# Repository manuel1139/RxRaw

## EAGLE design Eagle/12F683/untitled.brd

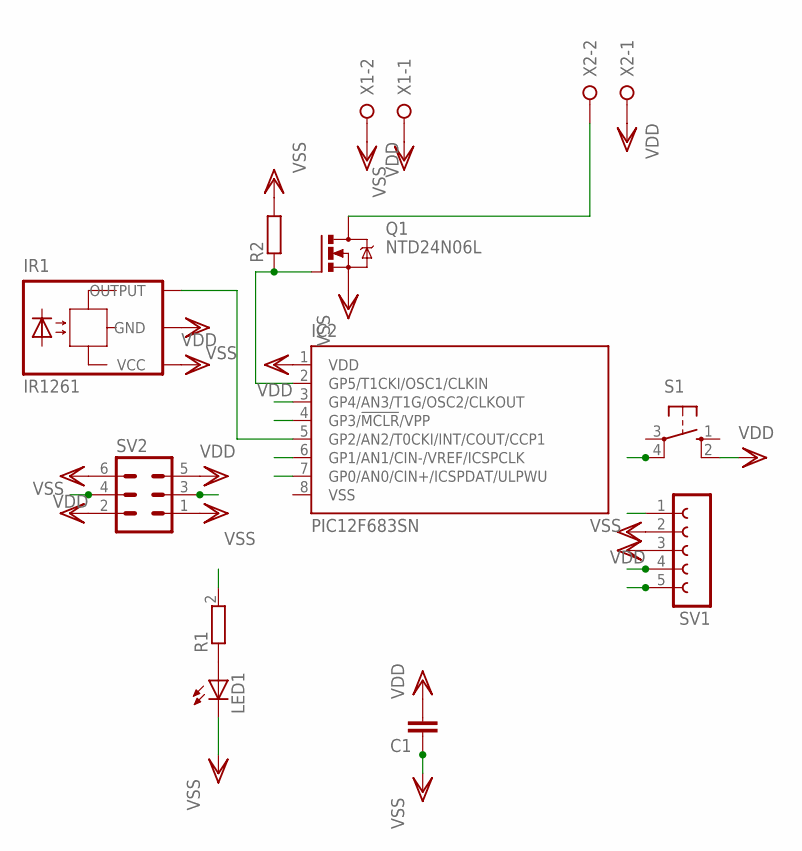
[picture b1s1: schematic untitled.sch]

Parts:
C1: C-EUC0805; C0805
IC2: PIC12F683SN; SO-08
IR1: IR1261
LED1: LEDCHIP-LED0603; CHIP-LED0603
Q1: NTD24N06L; D-PAK_TO252AA
R1: R0805_SMALL
R2: R-EU_R0805; R0805
S1: 10-XX; B3F-10XX
SV1: FE05-1
SV2: MA03-2
X1, X2: W237-02P; W237-132

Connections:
MCLR: IC2.4 (GP3/!MCLR!/VPP), SV1.1, SV2.4
unnamed: IC2.5 (GP2/AN2/T0CKI/INT/COUT/CCP1), IR1.VO (OUTPUT)
unnamed: LED1.A, R1.1 (A)
unnamed: IC2.2 (GP5/T1CKI/OSC1/CLKIN), Q1.1 (G), R2.1
unnamed: Q1.4 (D), X2.2
PGC: IC2.6 (GP1/AN1/CIN-/VREF/ICSPCLK), R1.2 (B), SV1.5
PGD: IC2.7 (GP0/AN0/CIN+/ICSPDAT/ULPWU), SV1.4, SV2.3
S1: IC2.3 (GP4/AN3/T1G/OSC2/CLKOUT), S1.4 (P1)
VDD: C1.2, IC2.1 (VDD), IR1.VCC, S1.2 (S1), SV1.2, SV2.5, SV2.6, X1.2, X2.1
VSS: C1.1, IC2.8 (VSS), IR1.GND, LED1.C, Q1.3 (S), R2.2, SV1.3, SV2.1, SV2.2, X1.1

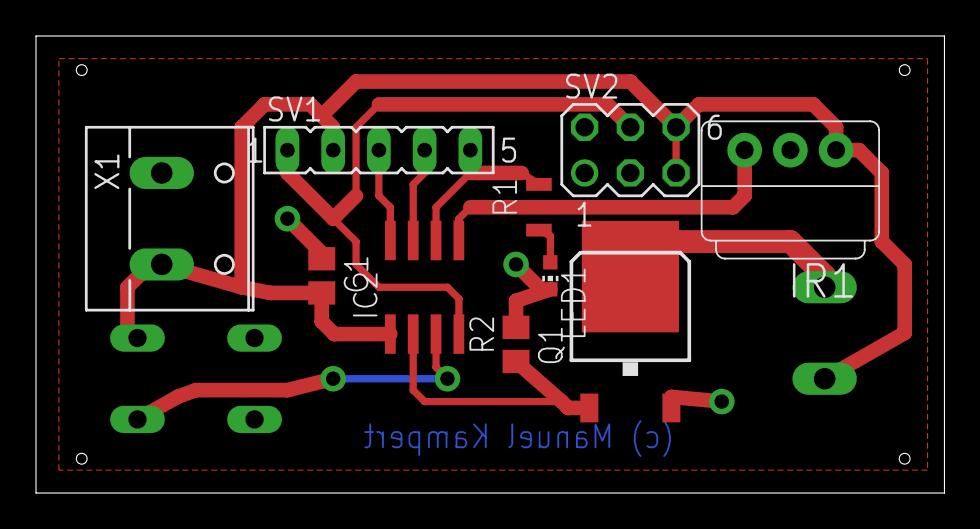
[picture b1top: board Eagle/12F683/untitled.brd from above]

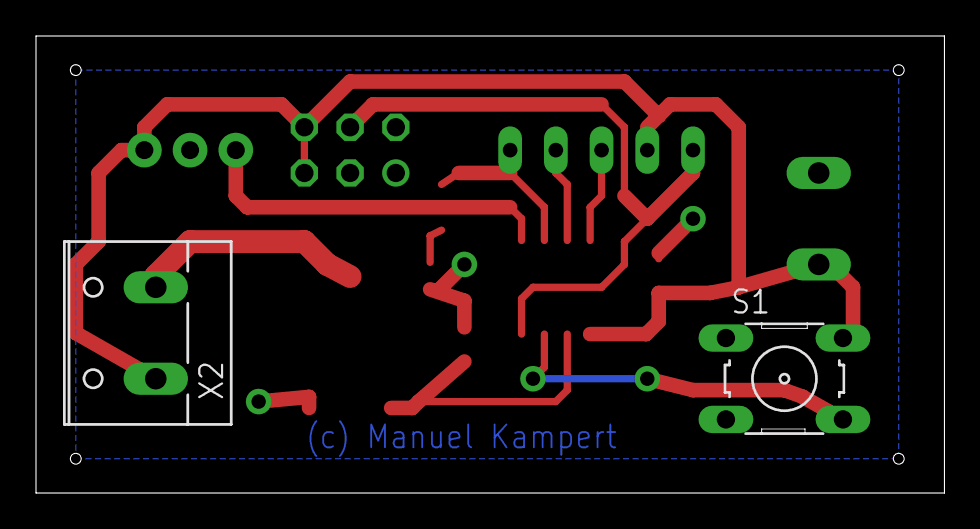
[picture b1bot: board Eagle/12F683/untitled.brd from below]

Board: 2 copper layers, 50.5 x 25.4 mm, 12 parts (2 on the bottom side), 10 nets.

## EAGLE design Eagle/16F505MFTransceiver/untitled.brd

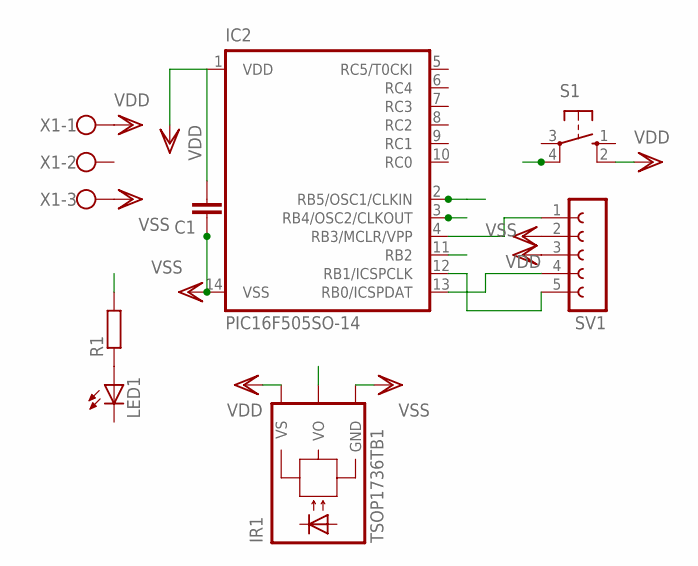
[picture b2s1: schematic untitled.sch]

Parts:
C1: C-EUC0805; C0805
IC2: PIC16F505SO-14; SO-14
IR1: TSOP1736TB1; TSOP17_TB1
LED1: LEDCHIP-LED0603; CHIP-LED0603
R1: R-EU_R0805; R0805
S1: 10-XX; B3F-10XX
SV1: FE05-1
X1: W237-103

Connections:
unnamed: IC2.4 (RB3/MCLR/VPP), SV1.1
unnamed: LED1.A, R1.1
unnamed: IC2.13 (RB0/ICSPDAT), SV1.4
unnamed: IC2.12 (RB1/ICSPCLK), SV1.5
RB2: IC2.11 (RB2), S1.4 (P1)
RB4: IC2.3 (RB4/OSC2/CLKOUT), R1.2
RB5: IC2.2 (RB5/OSC1/CLKIN), IR1.VO
VDD: C1.2, IC2.1 (VDD), IR1.VS, S1.2 (S1), SV1.2, X1.1
VSS: C1.1, IC2.14 (VSS), IR1.GND, SV1.3, X1.3

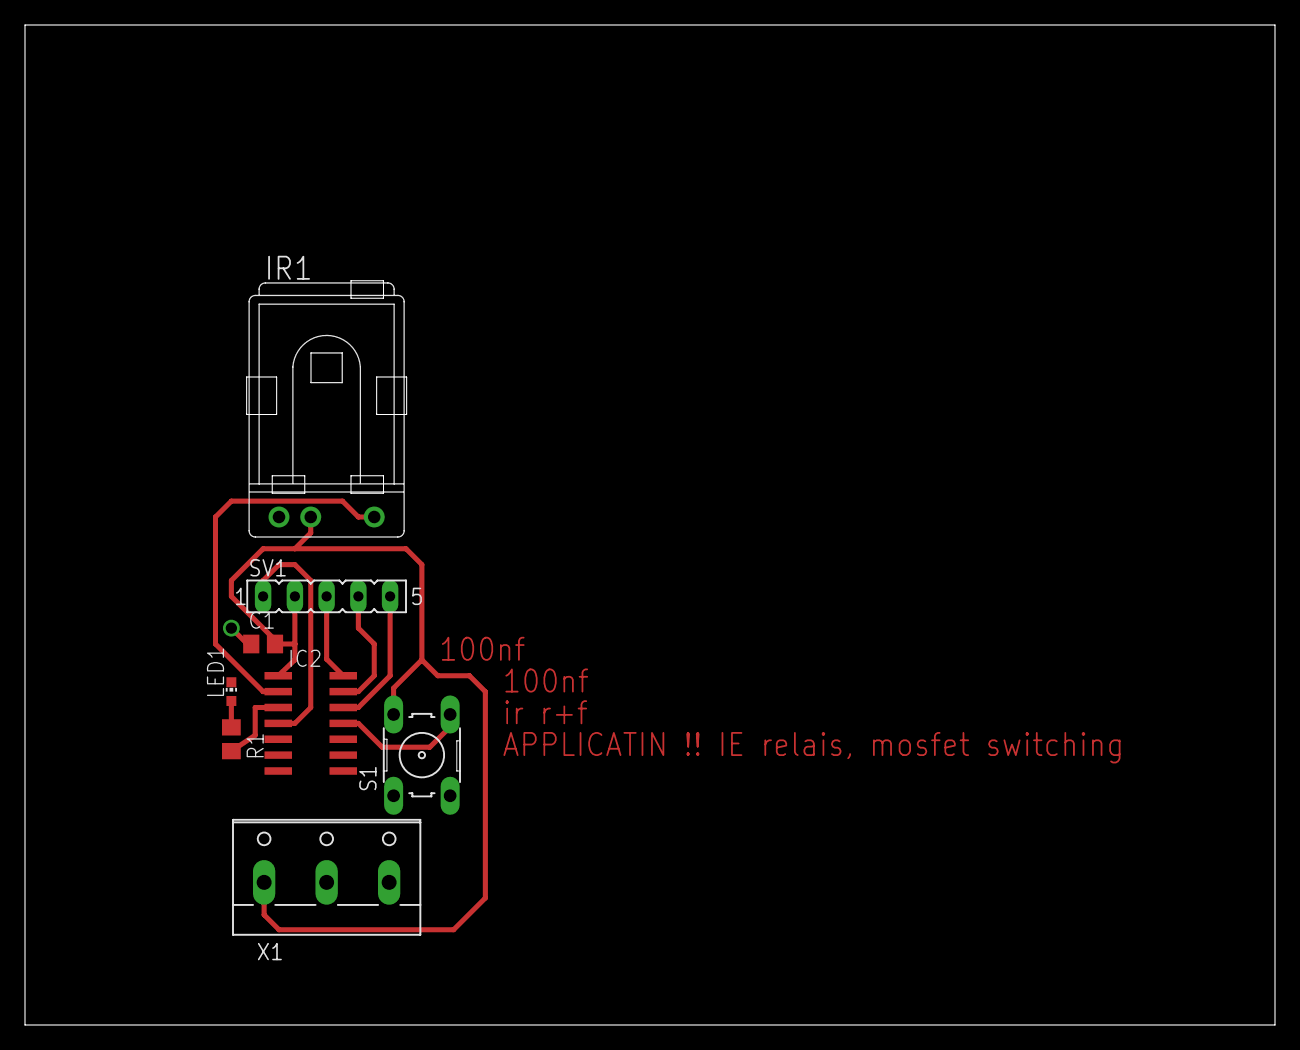
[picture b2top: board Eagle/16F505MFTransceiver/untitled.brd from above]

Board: 2 copper layers, 100.0 x 80.0 mm, 8 parts (0 on the bottom side), 9 nets.

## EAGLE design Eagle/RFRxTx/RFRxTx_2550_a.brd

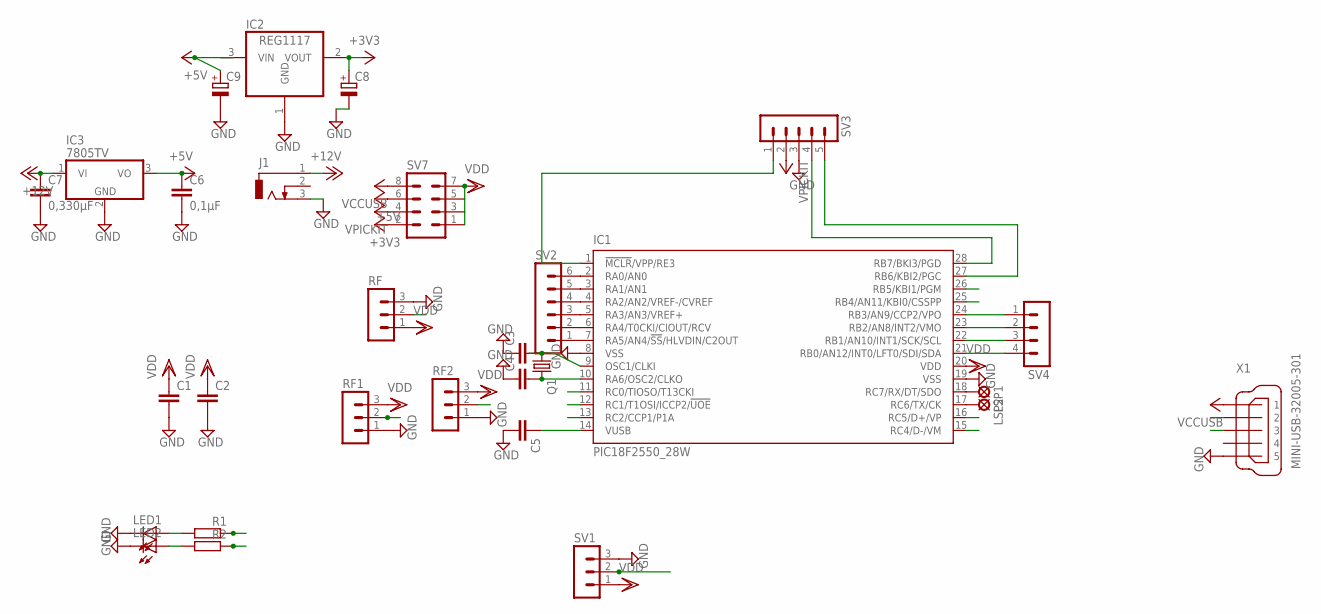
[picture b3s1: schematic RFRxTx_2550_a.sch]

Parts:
C1, C2, C3, C4, C5: C-EUC0805; C0805
C6: 0,1µF; C0805
C7: 0,330µF; C0805
C8, C9: CPOL-EU153CLV-0405; 153CLV-0405
IC1: PIC18F2550_28W; SO28W
IC2: REG1117; SOT223
IC3: 7805TV; TO220V
J1: DCJ0303
LED1, LED2: LED_ESML0603; LED_SML0603
LSP1, LSP2: LSP10
Q1: CRYSTALSM49; SM49
R1, R2: R-EU_R0805; R0805
RF, RF1, RF2: MA03-1
SV1: MA03-1
SV2: MA06-1
SV3: MA05-1
SV4: MA04-1
SV7: MA04-2
X1: MINI-USB-32005-301; 32005-301

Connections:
+3V3: C8.+, IC2.2 (VOUT), SV7.2
+5V: C6.1, C9.+, IC2.3 (VIN), IC3.3 (VO), SV7.6
+12V: C7.1, IC3.1 (VI), J1.1
CCP2: IC1.24 (RB3/AN9/CCP2/VPO), SV1.2, SV4.1
D+: IC1.16 (RC5/D+/VP), X1.3
D-: IC1.15 (RC4/D-/VM), X1.2
GND: C1.2, C2.2, C3.1, C4.1, C5.2, C6.2, C7.2, C8.-, C9.-, IC1.8 (VSS), IC1.19 (VSS), IC2.1 (GND), IC3.2 (GND), J1.3, LED1.C, LED2.C, RF.3, RF1.1, RF2.1, SV1.3, SV3.3, X1.5
IR: IC1.13 (RC2/CCP1/P1A), RF1.2
unnamed: IC1.7 (RA5/AN4/!SS!/HLVDIN/C2OUT), SV2.1
unnamed: IC1.6 (RA4/T0CKI/CIOUT/RCV), SV2.2
unnamed: IC1.5 (RA3/AN3/VREF+), SV2.3
unnamed: IC1.4 (RA2/AN2/VREF-/CVREF), SV2.4
unnamed: IC1.3 (RA1/AN1), SV2.5
unnamed: IC1.2 (RA0/AN0), SV2.6
unnamed: IC1.23 (RB2/AN8/INT2/VMO), SV4.2
unnamed: IC1.1 (!MCLR!/VPP/RE3), SV3.1
unnamed: IC1.28 (RB7/BKI3/PGD), SV3.4
unnamed: IC1.27 (RB6/KBI2/PGC), SV3.5
unnamed: IC1.22 (RB1/AN10/INT1/SCK/SCL), SV4.3
unnamed: IC1.21 (RB0/AN12/INT0/LFT0/SDI/SDA), SV4.4
unnamed: IC1.18 (RC7/RX/DT/SDO), LSP1.MP
unnamed: IC1.17 (RC6/TX/CK), LSP2.MP
unnamed: C4.2, IC1.10 (RA6/OSC2/CLKO), Q1.2
unnamed: C3.2, IC1.9 (OSC1/CLKI), Q1.1
unnamed: C5.1, IC1.14 (VUSB)
unnamed: LED1.A, R1.2
unnamed: LED2.A, R2.2
RB4: IC1.25 (RB4/AN11/KBI0/CSSPP), R2.1
RB5: IC1.26 (RB5/KBI1/PGM), R1.1
RC0: IC1.11 (RC0/TIOSO/T13CKI), RF2.2
RF: IC1.12 (RC1/T1OSI/ICCP2/!UOE), RF.2
VCC: SV3.2, SV7.4
VDD: C1.1, C2.1, IC1.20 (VDD), RF.1, RF1.3, RF2.3, SV1.1, SV7.1, SV7.3, SV7.5, SV7.7
VUSB: SV7.8, X1.1

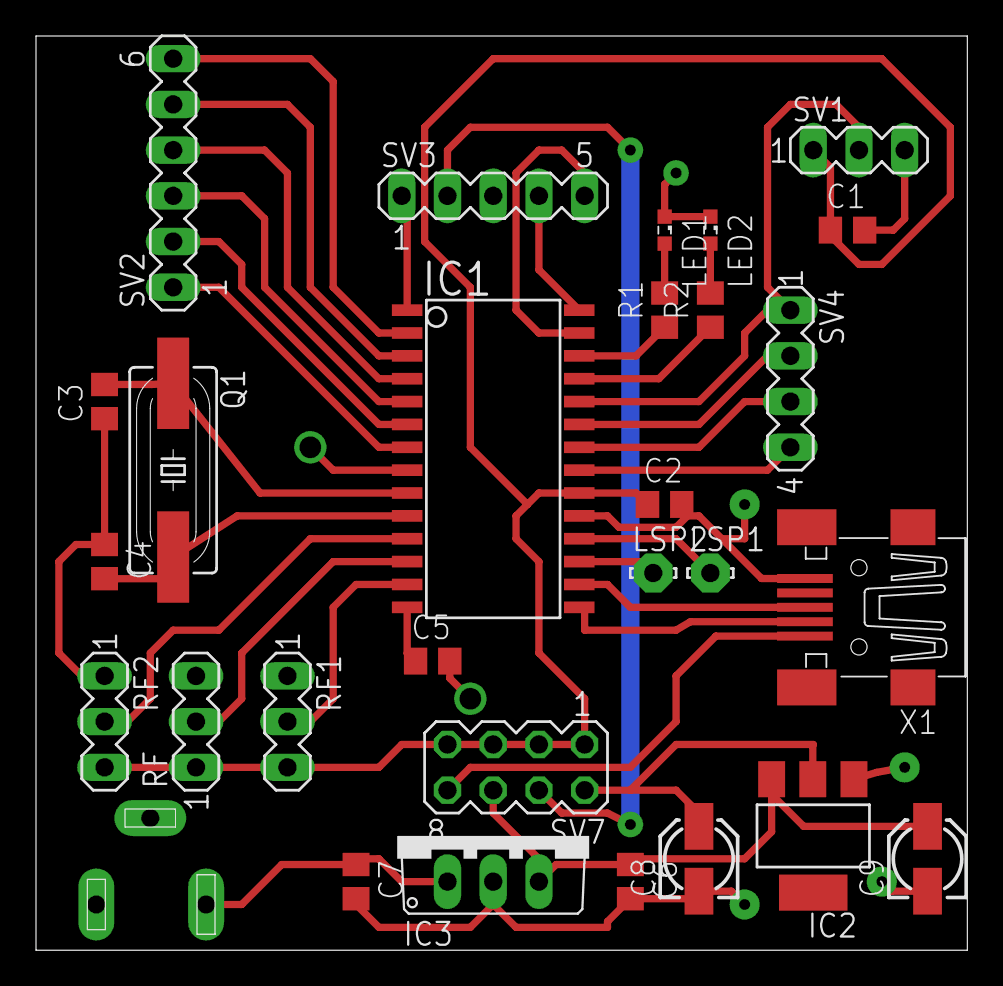
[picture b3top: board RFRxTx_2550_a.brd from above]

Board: 2 copper layers, 51.7 x 50.8 mm, 29 parts (1 on the bottom side), 34 nets.

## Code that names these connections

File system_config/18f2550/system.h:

/* 
 * File:   system.h
 * Author: manuel
 *
 * Created on 13. Juli 2016, 21:41
 */

#ifndef SYSTEM_H
#define	SYSTEM_H

#include "system_config.h"
#include "io_mapping.h"
#include "fixed_address_memory.h"
#include "usb_config.h"

#ifdef	__cplusplus
extern "C" {
#endif


#define OUTPUT_PIN 0
#define INPUT_PIN 1

/*
 * 
When Timer1 is enabled, the RC1/T1OSI/UOE and
RC0/T1OSO/T13CKI pins become inputs. This means
the values of TRISC<1:0> are ignored and the pins are
read as ?0?.
 */    
//#define IR_RCV_TRIS TRISCbits.TRISC2 see above timer1    
#define IR_RCV      PORTCbits.CCP1

#define DEAD_PIN_TRIS    TRISCbits.TRISC1
#define DEAD_PIN    PORTCbits.RC1
        
#define RF_OUT_TRIS TRISAbits.TRISA5
#define RF_OUT LATAbits.LATA5
    
#define IR_OUT_TRIS TRISBbits.TRISB3
#define IR_OUT LATBbits.RB3

#define LED1_TRIS TRISBbits.RB5
#define LED1 LATBbits.LB5

#define LED2_TRIS TRISBbits.RB4
#define LED2 LATBbits.LB4

    
    
    void SYSTEM_Initialize(void);

#ifdef	__cplusplus
}
#endif

#endif	/* SYSTEM_H */

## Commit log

2016-09-08 initial
2016-09-14 Merge origin/master
    Conflicts:
    nbproject/configurations.xml
2016-09-14 Merge origin/master
    Conflicts:
    main.c
2016-09-15 18f2550 working checked
